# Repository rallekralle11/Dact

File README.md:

# Dact

With overcurrent(short) and overvoltage protection on all IO pins, VIN reverse polarity and short protection, USB and MCU overcurrent protection as well as reset pin overvoltage protection. And USB-C.

Lacks 5 and 3V pin overvoltage protection, i tried but it wouldn't fit. Amazed i managed to fit this many features on it in general, and with 1608 components as well.

Of course there are tradeoffs, the onboard 5V regulator can only supply 150mA, there's no reset button and there's no way i could fit all pin identifiers, so i didn't add any.

Licensed under CERN-OHL-P

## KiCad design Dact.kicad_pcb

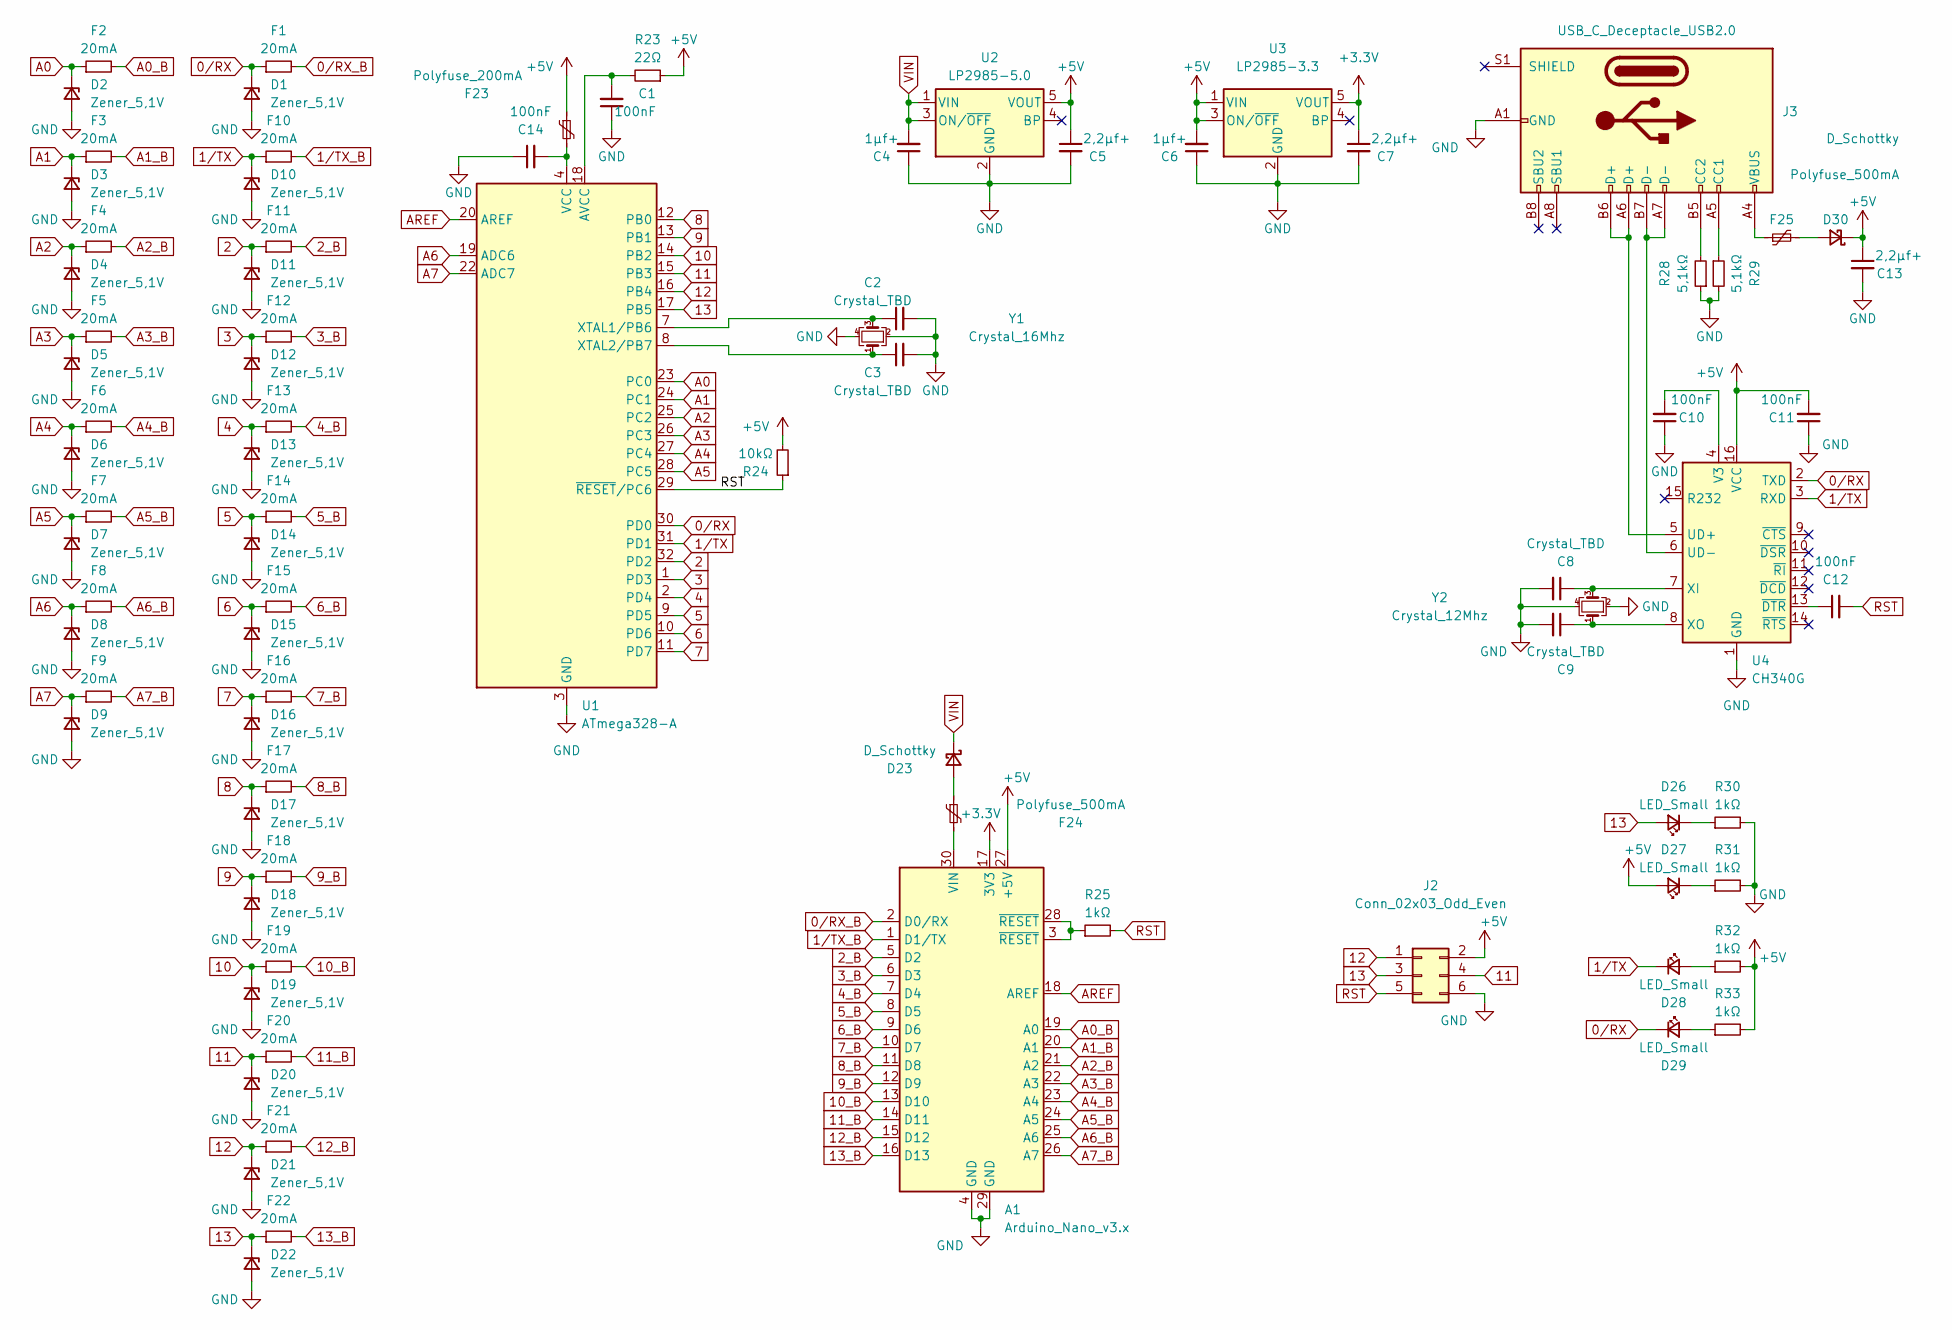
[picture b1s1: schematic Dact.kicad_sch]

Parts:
A1: Arduino_Nano_v3.x; Arduino_Nano
C1, C10, C11, C12, C14: 100nF; C_0603_1608Metric
C2, C3, C8, C9: Crystal_TBD; C_0603_1608Metric
C4, C6: 1µf+; C_0603_1608Metric
C5, C7, C13: 2,2µf+; C_0603_1608Metric
D1, D2, D3, D4, D5, D6, D7, D8, D9, D10, D11, D12, D13, D14, D15, D16, D17, D18, D19, D20, D21, D22: Zener_5,1V; SOD323_bättre
D23, D30: D_Schottky; SOD323_bättre
D26, D27, D28, D29: LED_Small; LED_0603_1608Metric
F1, F2, F3, F4, F5, F6, F7, F8, F9, F10, F11, F12, F13, F14, F15, F16, F17, F18, F19, F20, F21, F22: 20mA; R_0603_1608Metric
F23: Polyfuse_200mA; Fuse_1206_3216Metric
F24, F25: Polyfuse_500mA; Fuse_1206_3216Metric
J2: Conn_02x03_Odd_Even; PinHeader_2x03_P2.54mm_Vertical
J3: USB_C_Deceptacle_USB2.0; TYPE-C-SMD
R23: 22Ω; R_0603_1608Metric
R24: 10kΩ; R_0603_1608Metric
R25, R30, R31, R32, R33: 1kΩ; R_0603_1608Metric
R28, R29: 5,1kΩ; R_0603_1608Metric
U1: ATmega328-A; TQFP-32_7x7mm_P0.8mm
U2: LP2985-5.0; SOT-23-5
U3: LP2985-3.3; SOT-23-5
U4: CH340G; SOIC-16_3.9x9.9mm_P1.27mm
Y1: Crystal_16Mhz; Crystal_SMD_5032-4Pin_5.0x3.2mm
Y2: Crystal_12Mhz; Crystal_SMD_5032-4Pin_5.0x3.2mm

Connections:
0/RX: D1.1 (K), D29.1 (K), F1.1, U1.30 (PD0), U4.2 (TXD)
0/RX_B: A1.2 (D0/RX), F1.2
1/TX: D10.1 (K), D28.1 (K), F10.1, U1.31 (PD1), U4.3 (RXD)
1/TX_B: A1.1 (D1/TX), F10.2
2: D11.1 (K), F11.1, U1.32 (PD2)
2_B: A1.5 (D2), F11.2
3: D12.1 (K), F12.1, U1.1 (PD3)
3_B: A1.6 (D3), F12.2
4: D13.1 (K), F13.1, U1.2 (PD4)
4_B: A1.7 (D4), F13.2
5: D14.1 (K), F14.1, U1.9 (PD5)
5_B: A1.8 (D5), F14.2
6: D15.1 (K), F15.1, U1.10 (PD6)
6_B: A1.9 (D6), F15.2
7: D16.1 (K), F16.1, U1.11 (PD7)
7_B: A1.10 (D7), F16.2
8: D17.1 (K), F17.1, U1.12 (PB0)
8_B: A1.11 (D8), F17.2
9: D18.1 (K), F18.1, U1.13 (PB1)
9_B: A1.12 (D9), F18.2
10: D19.1 (K), F19.1, U1.14 (PB2)
10_B: A1.13 (D10), F19.2
11: D20.1 (K), F20.1, J2.4, U1.15 (PB3)
11_B: A1.14 (D11), F20.2
12: D21.1 (K), F21.1, J2.1, U1.16 (PB4)
12_B: A1.15 (D12), F21.2
13: D22.1 (K), D26.2 (A), F22.1, J2.3, U1.17 (PB5)
13_B: A1.16 (D13), F22.2
+3.3V: A1.17 (3V3), C7.1, U3.5 (VOUT)
+5V: A1.27 (+5V), C5.1, C6.2, C11.2, C13.1, D27.2 (A), D30.1 (K), F23.1, J2.2, R23.1, R24.2, R32.2, R33.2, U2.5 (VOUT), U3.1 (VIN), U3.3 (ON/~OFF), U4.16 (VCC)
A0: D2.1 (K), F2.1, U1.23 (PC0)
A0_B: A1.19 (A0), F2.2
A1: D3.1 (K), F3.1, U1.24 (PC1)
A1_B: A1.20 (A1), F3.2
A2: D4.1 (K), F4.1, U1.25 (PC2)
A2_B: A1.21 (A2), F4.2
A3: D5.1 (K), F5.1, U1.26 (PC3)
A3_B: A1.22 (A3), F5.2
A4: D6.1 (K), F6.1, U1.27 (PC4)
A4_B: A1.23 (A4), F6.2
A5: D7.1 (K), F7.1, U1.28 (PC5)
A5_B: A1.24 (A5), F7.2
A6: D8.1 (K), F8.1, U1.19 (ADC6)
A6_B: A1.25 (A6), F8.2
A7: D9.1 (K), F9.1, U1.22 (ADC7)
A7_B: A1.26 (A7), F9.2
AREF: A1.18 (AREF), U1.20 (AREF)
GND: A1.4 (GND), A1.29 (GND), C1.1, C2.2, C3.2, C4.1, C5.2, C6.1, C7.2, C8.2, C9.2, C10.1, C11.1, C13.2, C14.1, D1.2 (A), D2.2 (A), D3.2 (A), D4.2 (A), D5.2 (A), D6.2 (A), D7.2 (A), D8.2 (A), D9.2 (A), D10.2 (A), D11.2 (A), D12.2 (A), D13.2 (A), D14.2 (A), D15.2 (A), D16.2 (A), D17.2 (A), D18.2 (A), D19.2 (A), D20.2 (A), D21.2 (A), D22.2 (A), J2.6, J3.A1 (GND), J3.A12 (GND), J3.B1 (GND), J3.B12 (GND), R28.1, R29.2, R30.2, R31.2, U1.3 (GND), U1.5 (GND), U1.21 (GND), U2.2 (GND), U3.2 (GND), U4.1 (GND), Y1.2, Y1.4, Y2.2, Y2.4
unnamed: A1.3 (~RESET), A1.28 (~RESET), R25.1
unnamed: A1.30 (VIN), F24.2
unnamed: C1.2, R23.2, U1.18 (AVCC)
unnamed: C2.1, U1.7 (XTAL1/PB6), Y1.3
unnamed: C3.1, U1.8 (XTAL2/PB7), Y1.1
unnamed: C8.1, U4.7 (XI), Y2.3
unnamed: C9.1, U4.8 (XO), Y2.1
unnamed: C10.2, U4.4 (V3)
unnamed: C12.1, U4.13 (~DTR)
unnamed: C14.2, F23.2, U1.4 (VCC), U1.6 (VCC)
unnamed: D23.2 (A), F24.1
unnamed: D26.1 (K), R30.1
unnamed: D27.1 (K), R31.1
unnamed: D28.2 (A), R32.1
unnamed: D29.2 (A), R33.1
unnamed: D30.2 (A), F25.2
unnamed: F25.1, J3.A4 (VBUS), J3.A9 (VBUS), J3.B4 (VBUS), J3.B9 (VBUS)
unnamed: J3.A5 (CC1), R29.1
unnamed: J3.A6 (D+), J3.B6 (D+), U4.5 (UD+)
unnamed: J3.A7 (D-), J3.B7 (D-), U4.6 (UD-)
unnamed: J3.B5 (CC2), R28.2
RST: C12.2, J2.5, R24.1, R25.2, U1.29 (~RESET/PC6)
VIN: C4.2, D23.1 (K), U2.1 (VIN), U2.3 (ON/~OFF)

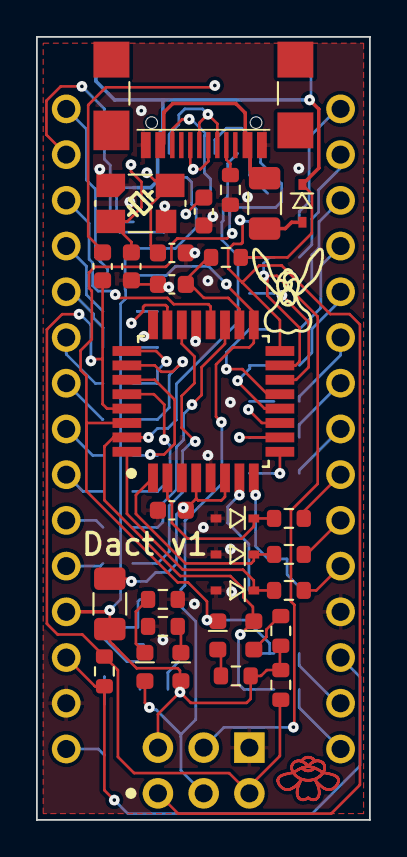
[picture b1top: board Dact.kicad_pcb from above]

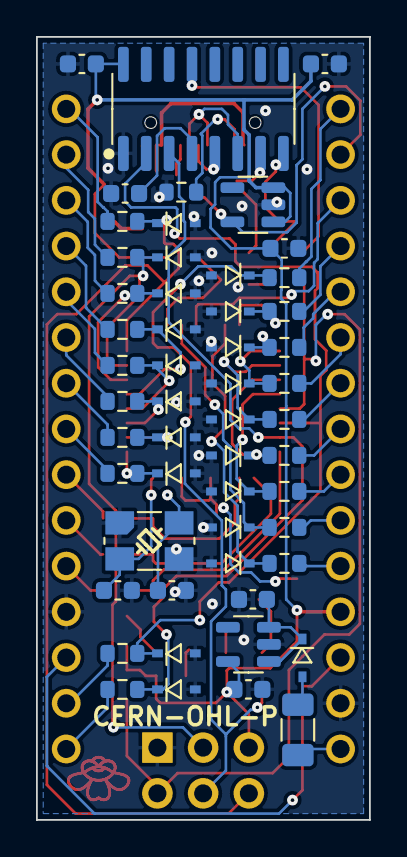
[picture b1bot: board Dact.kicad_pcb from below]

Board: 2 copper layers, 18.5 x 43.5 mm, 85 parts (53 on the bottom side), 71 nets.

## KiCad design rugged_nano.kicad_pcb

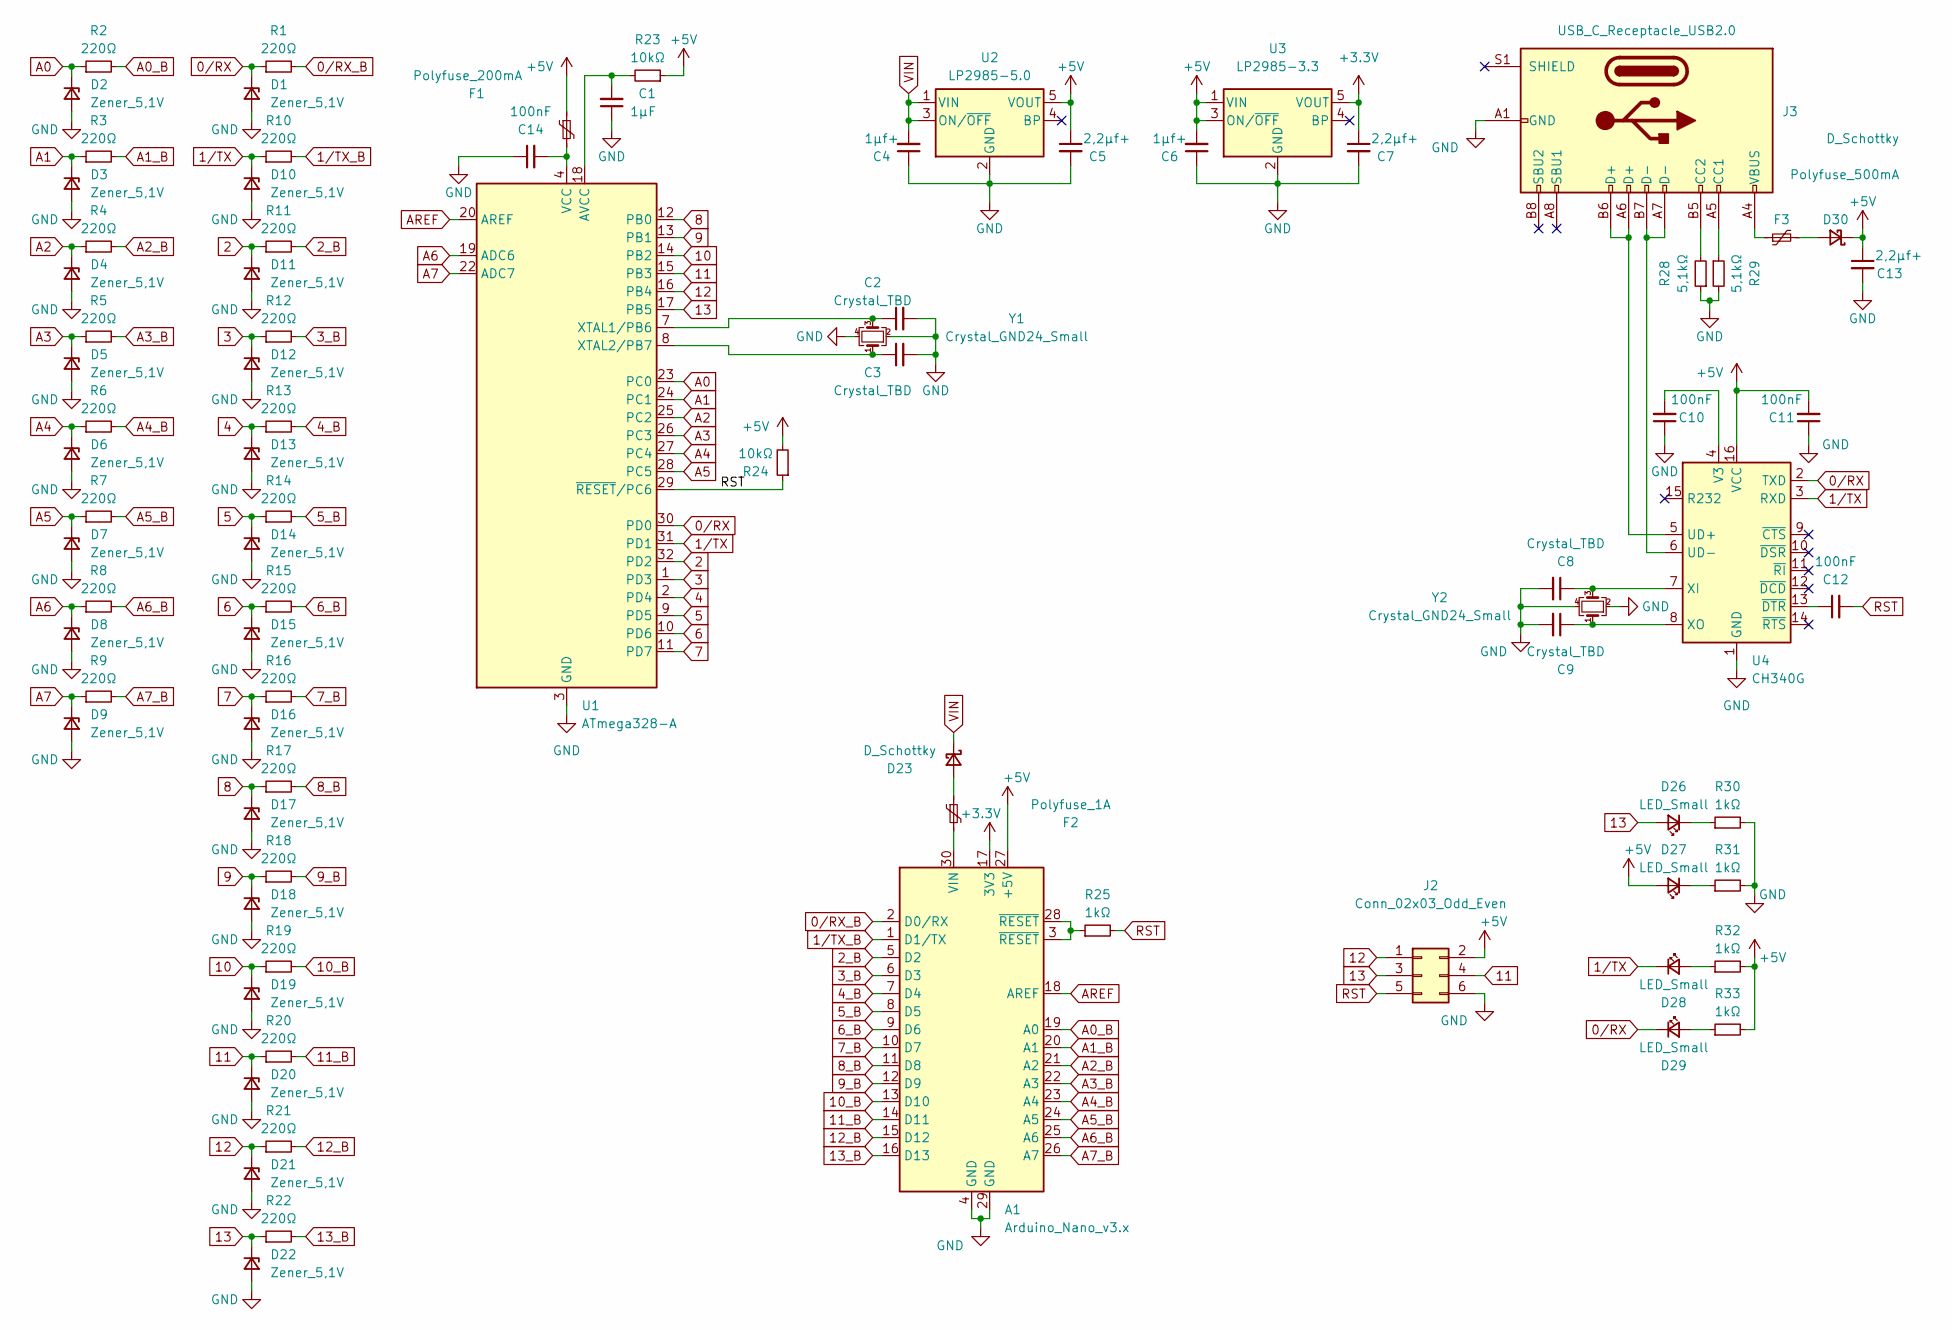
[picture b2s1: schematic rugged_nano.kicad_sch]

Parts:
A1: Arduino_Nano_v3.x; Arduino_Nano
C1: 1µF; C_0603_1608Metric
C2, C3, C8, C9: Crystal_TBD; C_0603_1608Metric
C4, C6: 1µf+; C_0603_1608Metric
C5, C7, C13: 2,2µf+; C_0603_1608Metric
C10, C11, C12, C14: 100nF; C_0603_1608Metric
D1, D2, D3, D4, D5, D6, D7, D8, D9, D10, D11, D12, D13, D14, D15, D16, D17, D18, D19, D20, D21, D22: Zener_5,1V; SOD323_bättre
D23, D30: D_Schottky; SOD323_bättre
D26, D27, D28, D29: LED_Small; LED_0603_1608Metric
F1: Polyfuse_200mA; Fuse_1206_3216Metric
F2: Polyfuse_1A; Fuse_1206_3216Metric
F3: Polyfuse_500mA; Fuse_1206_3216Metric
J2: Conn_02x03_Odd_Even; PinHeader_2x03_P2.54mm_Vertical
J3: USB_C_Receptacle_USB2.0; TYPE-C-SMD
R1, R2, R3, R4, R5, R6, R7, R8, R9, R10, R11, R12, R13, R14, R15, R16, R17, R18, R19, R20, R21, R22: 220Ω; R_0603_1608Metric
R23, R24: 10kΩ; R_0603_1608Metric
R25, R30, R31, R32, R33: 1kΩ; R_0603_1608Metric
R28, R29: 5,1kΩ; R_0603_1608Metric
U1: ATmega328-A; TQFP-32_7x7mm_P0.8mm
U2: LP2985-5.0; SOT-23-5
U3: LP2985-3.3; SOT-23-5
U4: CH340G; SOIC-16_3.9x9.9mm_P1.27mm
Y1, Y2: Crystal_GND24_Small; Crystal_SMD_5032-4Pin_5.0x3.2mm

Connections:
0/RX: D1.1 (K), D29.1 (K), R1.1, U1.30 (PD0), U4.2 (TXD)
0/RX_B: A1.2 (D0/RX), R1.2
1/TX: D10.1 (K), D28.1 (K), R10.1, U1.31 (PD1), U4.3 (RXD)
1/TX_B: A1.1 (D1/TX), R10.2
2: D11.1 (K), R11.1, U1.32 (PD2)
2_B: A1.5 (D2), R11.2
3: D12.1 (K), R12.1, U1.1 (PD3)
3_B: A1.6 (D3), R12.2
4: D13.1 (K), R13.1, U1.2 (PD4)
4_B: A1.7 (D4), R13.2
5: D14.1 (K), R14.1, U1.9 (PD5)
5_B: A1.8 (D5), R14.2
6: D15.1 (K), R15.1, U1.10 (PD6)
6_B: A1.9 (D6), R15.2
7: D16.1 (K), R16.1, U1.11 (PD7)
7_B: A1.10 (D7), R16.2
8: D17.1 (K), R17.1, U1.12 (PB0)
8_B: A1.11 (D8), R17.2
9: D18.1 (K), R18.1, U1.13 (PB1)
9_B: A1.12 (D9), R18.2
10: D19.1 (K), R19.1, U1.14 (PB2)
10_B: A1.13 (D10), R19.2
11: D20.1 (K), J2.4, R20.1, U1.15 (PB3)
11_B: A1.14 (D11), R20.2
12: D21.1 (K), J2.1, R21.1, U1.16 (PB4)
12_B: A1.15 (D12), R21.2
13: D22.1 (K), D26.2 (A), J2.3, R22.1, U1.17 (PB5)
13_B: A1.16 (D13), R22.2
+3.3V: A1.17 (3V3), C7.1, U3.5 (VOUT)
+5V: A1.27 (+5V), C5.1, C6.2, C11.2, C13.1, D27.2 (A), D30.1 (K), F1.1, J2.2, R23.1, R24.2, R32.2, R33.2, U2.5 (VOUT), U3.1 (VIN), U3.3 (ON/~OFF), U4.16 (VCC)
A0: D2.1 (K), R2.1, U1.23 (PC0)
A0_B: A1.19 (A0), R2.2
A1: D3.1 (K), R3.1, U1.24 (PC1)
A1_B: A1.20 (A1), R3.2
A2: D4.1 (K), R4.1, U1.25 (PC2)
A2_B: A1.21 (A2), R4.2
A3: D5.1 (K), R5.1, U1.26 (PC3)
A3_B: A1.22 (A3), R5.2
A4: D6.1 (K), R6.1, U1.27 (PC4)
A4_B: A1.23 (A4), R6.2
A5: D7.1 (K), R7.1, U1.28 (PC5)
A5_B: A1.24 (A5), R7.2
A6: D8.1 (K), R8.1, U1.19 (ADC6)
A6_B: A1.25 (A6), R8.2
A7: D9.1 (K), R9.1, U1.22 (ADC7)
A7_B: A1.26 (A7), R9.2
AREF: A1.18 (AREF), U1.20 (AREF)
GND: A1.4 (GND), A1.29 (GND), C1.1, C2.2, C3.2, C4.1, C5.2, C6.1, C7.2, C8.2, C9.2, C10.1, C11.1, C13.2, C14.1, D1.2 (A), D2.2 (A), D3.2 (A), D4.2 (A), D5.2 (A), D6.2 (A), D7.2 (A), D8.2 (A), D9.2 (A), D10.2 (A), D11.2 (A), D12.2 (A), D13.2 (A), D14.2 (A), D15.2 (A), D16.2 (A), D17.2 (A), D18.2 (A), D19.2 (A), D20.2 (A), D21.2 (A), D22.2 (A), J2.6, J3.A1 (GND), J3.A12 (GND), J3.B1 (GND), J3.B12 (GND), R28.1, R29.2, R30.2, R31.2, U1.3 (GND), U1.5 (GND), U1.21 (GND), U2.2 (GND), U3.2 (GND), U4.1 (GND), Y1.2, Y1.4, Y2.2, Y2.4
unnamed: A1.3 (~RESET), A1.28 (~RESET), R25.1
unnamed: A1.30 (VIN), F2.2
unnamed: C1.2, R23.2, U1.18 (AVCC)
unnamed: C2.1, U1.7 (XTAL1/PB6), Y1.3
unnamed: C3.1, U1.8 (XTAL2/PB7), Y1.1
unnamed: C8.1, U4.7 (XI), Y2.3
unnamed: C9.1, U4.8 (XO), Y2.1
unnamed: C10.2, U4.4 (V3)
unnamed: C12.1, U4.13 (~DTR)
unnamed: C14.2, F1.2, U1.4 (VCC), U1.6 (VCC)
unnamed: D23.2 (A), F2.1
unnamed: D26.1 (K), R30.1
unnamed: D27.1 (K), R31.1
unnamed: D28.2 (A), R32.1
unnamed: D29.2 (A), R33.1
unnamed: D30.2 (A), F3.2
unnamed: F3.1, J3.A4 (VBUS), J3.A9 (VBUS), J3.B4 (VBUS), J3.B9 (VBUS)
unnamed: J3.A5 (CC1), R29.1
unnamed: J3.A6 (D+), J3.B6 (D+), U4.5 (UD+)
unnamed: J3.A7 (D-), J3.B7 (D-), U4.6 (UD-)
unnamed: J3.B5 (CC2), R28.2
RST: C12.2, J2.5, R24.1, R25.2, U1.29 (~RESET/PC6)
VIN: C4.2, D23.1 (K), U2.1 (VIN), U2.3 (ON/~OFF)

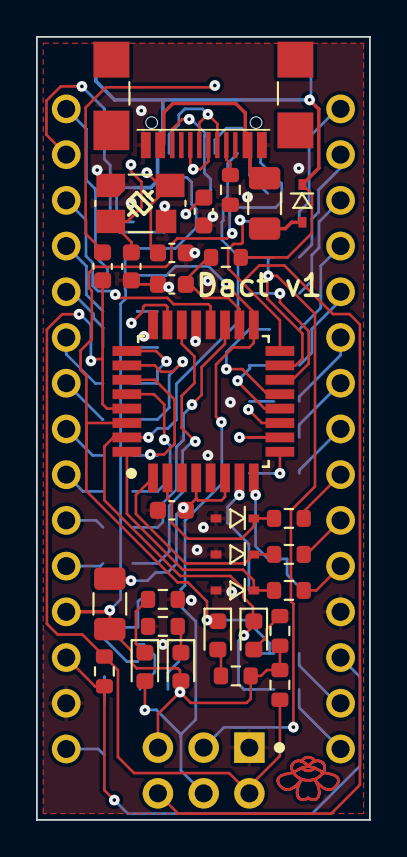
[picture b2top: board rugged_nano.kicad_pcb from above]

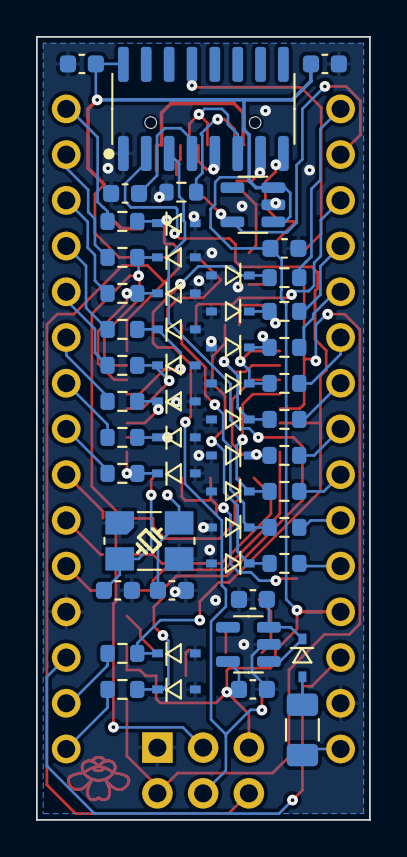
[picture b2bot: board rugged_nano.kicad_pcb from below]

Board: 2 copper layers, 18.5 x 43.5 mm, 85 parts (53 on the bottom side), 71 nets.

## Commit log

2022-12-14 bit of everything
2022-12-14 small changes
2022-12-14 tiny change
2022-12-15 updated gerbers
2022-12-17 redid some designators and things
2023-01-06 BOM update
2023-02-07 slight update
